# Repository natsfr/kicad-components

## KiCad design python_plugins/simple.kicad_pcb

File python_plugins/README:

Use of foot print wizard:
 - Linux: ~/.kicad_plugins/
 - Windows: InstallPath\KiCad\share\kicad\scripting\plugins

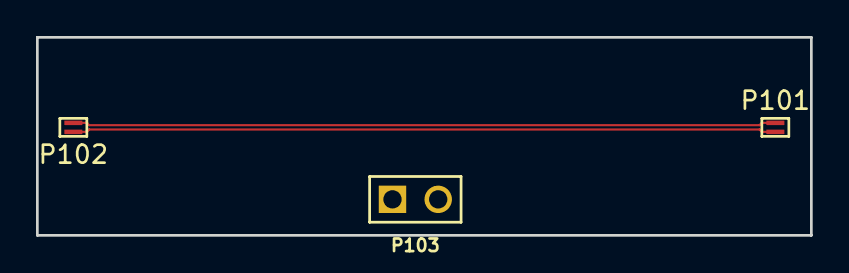
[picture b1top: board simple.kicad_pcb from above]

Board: 2 copper layers, 43.0 x 11.0 mm, 3 parts (0 on the bottom side), 3 nets.

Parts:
P101, P102: CONN_01X02; TEST_01x02_05mm
P103: CONN_01X02; pin_array_2x1

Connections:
/HS_N: P101.2, P102.1
/HS_P: P101.1, P102.2
GND: P103.1, P103.2

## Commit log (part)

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2010-10-10 Init repository
2010-10-11 Added Pic18F2xK20 schematic
2010-10-11 Added XC9572XL Schematic (vqfp44, pc44) and VQFP44 Footprint
2010-10-11 Added Maxim DS1077 Osc and NS LM2734 Buck converter.
2011-03-09 Added Microchip TC105 buck converter
2011-03-15 Added TPS76333 LDO
2011-03-15 Added LM2940
2011-03-15 Add MCP3201 - MCP1541 - PIC18LF1XK22
2012-07-23 Add MP2562DS SOIC8 schematic
2012-07-23 Add uSD-Card connector and hanrun magjack
2013-10-24 Added Silabs Si446x schematic and STM32F103RG schematic
2015-02-02 added PMSRE parts
2015-02-02 added xtals resistors and drv88(
2015-02-04 added lm27313, reg113, stm32f103tb
2015-02-04 Rename resistors.lib to passives.lib
2015-02-08 added usky project parts
2015-02-09 added tag connect TC2030-NL
2015-02-12 starts of spartan 6 FT256
2015-02-12 add TL972 op-amp
2015-02-17 added bank2
2015-02-19 added bank3 and jtag
2015-02-20 xc6slx9-25 done
2015-02-20 corrected si44-x schematic | added more fixed package capacitor and inductor
2015-02-22 added xtal and modification stm32f103tb
2015-02-23 added generated FT256 BGA package
2015-02-23 removed local clearance from FT256
2015-02-24 Added CSMALL for compatibility with old projects
2015-02-24 added first pretty kicad module
2015-02-25 adding qfn plugin for kicad
2015-02-26 silkscreen bug + IO file error
2015-02-26 Update and rename python_plugins to python_plugins/README
2015-02-26 added quick illustratiuon for qfn generator
2015-02-26 starting add of thermal via
2015-02-26 added thermal via, and added silscreen corner
2015-02-26 added picture 3 for qfn generator
2015-02-26 corrected boolean bug. Thx @inductiveload
2015-02-26 use previous version this one is a WIP
2015-02-26 paste is badly aligned
2015-02-27 debugging paste placement
2015-02-27 adding paste box function
2015-02-27 repaired conflict made with myself
2015-02-27 repaired conflict ?
2015-03-02 works with the help of pcbnew_easy.py need to think about integrating it
2015-03-02 working stand alone script
2015-03-05 added older power symbol for compatibility
2015-03-15 added a bunch of footprints
2015-03-29 add standard SOT23
2015-04-02 added HMC422MS8E mixer
2015-04-03 added si4133 pll
2015-04-13 add max4389 amplifier and BGA256 footprint
2015-04-13 add 0603 inductor
2015-04-14 add MAX5190/87
2015-04-14 finished MAX5190 lib
2015-04-14 added opa2381
2015-04-16 corrected lib
2015-04-16 added msop8
2015-04-16 added hmc629lp4
2015-04-17 added sexy footprint
2015-04-17 added sma footprint
2015-04-19 added standard tcxo symbol
2015-04-20 added jtag arm connector + corrected some qfn footprint
2015-04-21 added GND pad connection on qfn
2015-08-02 Added adl9114 and adl5375
2015-08-02 added ADRF6702
2015-08-03 added SI1102 + mounting hole
2015-08-07 added 1206 capcitor
2015-08-07 Add QFN 40 LFCSP
2015-08-09 Adding SST25 (generic spi flash)
2015-08-09 added Atmel SAM3UxC symbol
2015-08-09 adding 0402/SOIC8/DM3CS footprints
2015-08-11 add AS213-92 rf switch symbol
2015-08-11 adding jtag connectors
2015-08-12 add qfn 24
2015-08-13 adding SF1186
2015-08-13 changed shield pin
2015-08-14 adding se4110l
2015-08-15 added dc jack
2015-08-16 Adding DCC6C, SAW filter
2015-08-17 Corrected error TDO is 54 not 52
2015-08-23 adding hole and usb
2015-09-10 start an ODB++ exporter for kicad
2015-09-11 PADS listing
2015-09-16 continuing component ODB export
2015-09-16 pouet'
2015-09-16 Changing model
2015-09-17 using list
2016-04-11 moved csv2lib util from an other git repo
2016-04-12 csv2lib now reorder at zero for each unit in symbol
2016-04-12 added XC7A15T FGG484 symbol
2016-04-13 Updated windows install path for plugin
2016-04-13 Added FMC HPC Male footprint
2016-04-14 starting genesys2 fmc
2016-04-14 almost done symbol
2016-04-14 done connector
2016-04-15 added ti redriver, sfp symbol
2016-04-17 adding custom QFN24 footprint
2016-04-18 blabla
2016-04-18 added stuff
2016-04-19 adding pin array
2016-04-19 correcting SFP problem
2016-04-20 added various symbol
2016-04-21 adding si5338 symbol
2016-04-21 added an other qfn24 footprint :D
2016-04-22 added a Vadj symbol
2016-04-24 adding sata symbol
2016-04-25 sata footprint
2016-04-25 changed 0603 LED Footprint
2016-08-03 added buf634
2016-10-07 adding
2016-10-10 adding PGA145 and PB1024
2016-10-10 added 32 pin array
2016-10-11 corrected pb1024 E2/F2 pin
2016-10-11 adding EC capacitor
2016-10-12 reversed PGA145 ! need to be updated !
2016-10-12 reversed side
2016-10-19 adding crap :))
2016-10-19 adding fpc connector
2016-10-19 add pic24jf
2016-10-20 sot-236 0.95mm
2017-02-22 adding TCA0372 DW version
2017-02-23 corrected tca0372, added SOIC16 and SMA antenna
2017-09-27 added backlog
2017-09-28 adding begins of adf5355
2017-10-06 adding various RF components
2017-10-06 restore qfn wizard
2017-10-10 adding mini circuits package
2017-10-22 adding components
2017-10-24 AD8130
2017-11-07 adding LTC2271
2017-11-17 add various rf chip
2017-11-19 add RF stuff
2017-11-21 add adm7170
2017-11-23 adding diff xo symbol
2017-11-26 add dcdc
2017-12-03 add QFN16 footprint
2017-12-03 qfn footprint
2017-12-05 adding few footprintsé
2017-12-07 added feature to the QFN Wizard
2017-12-07 added non centered thermal pad support
2017-12-08 corrected paste area on qfn pad
2017-12-08 adding QFN52 footprint
2017-12-17 corrected few footprint
2018-01-18 added circular hole for Jack
2018-03-19 adding component for labclock
2018-03-22 added uFL connector
2018-03-23 misc part
2018-05-07 adding part for the 435MHz Fusex PA
2018-05-08 adding lx25 in BGA
2018-05-21 added symbol fo shield
2018-05-31 no idea of what I'm doing
2018-05-31 added qfn
2018-06-11 adding spino component
2018-06-11 added mini circuit BH292 FP
2018-06-12 SOIC 8 208mil
2018-06-17 adding various part
2018-06-18 adding NB6L11S
2018-06-18 blabla usefull commit comment
2018-06-24 added DSN components
2018-06-24 adding part for VNA V2
2018-08-28 adding MGA_43228 symbol
2018-08-30 starting ltc2157 symbol
2018-09-04 finished ltc2157 symbol
2018-09-10 corrected ltc2157 symbol
2018-09-16 adding WBC1-1TL transformer
2018-09-16 adding AD5205
2018-09-21 added adl5387
2018-09-22 adding RF devices
2018-09-23 adding footprint
2018-09-26 adding rf switch
2018-10-02 adding rf stuff
2018-10-18 adding radio stuff
2018-10-25 adding footprint for PA board
2018-11-02 finished and verified symbol for AD9363
2018-11-04 adding few power symbol
2018-11-05 finalized AD9363 and footprint
2018-11-07 Power and testpoint
2018-11-28 adding sx125x
2018-12-04 adding LGA footprint for power module
2018-12-05 adding bidir level shifter
2018-12-06 adding a bunch of LDO and connector footprint
2018-12-07 adding a bunch of crap
2018-12-14 adding sc75 footprint
2018-12-17 adding skyworks lna
2019-01-06 starting MDR26
2019-02-07 adding parts
2019-02-07 adding switch
2019-02-08 adding 3W transceiver part
2019-02-12 Working footprint
2019-02-13 added few microstrip trace and footprint
2019-02-17 adding footprint for vna layout
2019-03-04 adding few footprint
2019-03-06 correcting pin type for passive parts
2019-03-14 added a lot of footprint
2019-03-14 adding 3D models
2019-03-21 corrected symbol
2019-03-26 adding new bergstak
2019-03-26 adding AD9747
2019-03-31 corrected footprint
2019-04-01 adding logic and gate
2019-04-04 adding qfn footprint
2019-04-25 lot of parts
2019-04-28 added misc part
2019-05-05 added few part
2019-05-07 added pmos
2019-05-17 a lot of 3D model
2019-05-19 adding stencil align hole
2019-05-24 adding samtec stuff
2019-05-28 added new models
2019-05-29 corrected 3D Models Path, please define CUSTLIB var in kicad project !
2019-06-12 adding samtech connector
2019-06-24 adding nanofit connector
2019-06-25 adding connector
2019-06-27 harting
2019-07-01 modified QSE footprint
2019-07-02 adding PoL
2019-07-05 added GVA-81+
2019-07-08 corrected some pad
2019-07-10 update DF782
2019-07-18 adding RPI footprint
2019-08-28 adding news QFN generator version
2019-08-30 adding sky pa
2019-09-05 adding QTE 8mm heigth
2019-09-05 adding lot of minicircuit component
2019-09-26 adding a bunch of 3D models
2019-09-26 footprint
2019-10-08 adding lot of RF stuff
2019-10-10 modified stuff
2019-10-15 adding limiter
2019-11-14 adding a lot of model
2019-11-22 cleaned and added 3D model for connector and various part
2019-11-29 correcting silkscreen on DHVQFN footprint
2019-12-10 adding mouser sku
2019-12-11 adding dc motor driver
2020-02-24 adding filter and 3D model
2020-06-26 Adding bunch of component
2020-07-17 adding ADI pll
2020-07-17 Modified LFCN symbol (adding footprint reference) and adding MCL part
2020-07-20 correctingsome footprint, incoming big rework of all the library !
2020-07-21 Adding minicircuit footprint
2020-07-22 updating mini circuit footprint
2020-07-24 updated realay 3D model
2020-07-26 correcting component
2020-09-09 adding FT601 schematic
2020-09-13 adding power symbol
2020-09-15 adding usb3 connector
2020-09-30 adding models
2020-10-20 adding news component
2020-10-22 adding rf part
2021-02-18 updated footprint
2021-05-01 pushing a bunch of RF component
2021-05-31 adding new part
2021-07-16 adding vref
2021-10-07 VFO Dial component
2021-11-10 wouhou bunch of crunchy component
2021-11-10 always more component
2021-12-20 updating and adding a bunch, will change repo soon
2021-12-28 bunch of components
2022-01-17 adding stuff
2022-03-03 misc component
2022-06-30 adding bunch of part
2022-07-30 adding mega bunch of part
2022-08-24 Adding LDO
2022-09-02 adding comparator
2022-11-18 bunch of part
2023-02-09 an other bunch of components
2023-04-04 Updates the Better QFN generator for kicad 7
2023-04-07 a lot of crap to commit
2023-07-09 adding 7606C
2023-09-03 bunch of parts
2023-09-05 fast commit
2023-10-16 adding few symbol
2023-11-21 adding part
2023-11-22 adding coil
2024-02-25 adding TE champ connector
2024-07-31 add a bunch of part
2024-08-06 adding a bunch of part
2024-09-05 adding package
2024-11-23 adding aprt
2025-04-22 pico ezmate
2025-05-14 add footprint
2025-05-26 updating my advanced QFN plugin for Kicad 9.0
2025-05-28 adding new symbol
2025-07-04 adding bunch of parts
2025-07-10 correcting footprint
2025-07-21 correcting foot print
2026-01-27 led package fix
2026-01-30 converting libs
2026-02-17 adding symbol and package
2026-03-04 correcting schematic
2026-05-17 improving footprint
